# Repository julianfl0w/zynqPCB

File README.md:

# zynqPCB
An 8-layer board built upon Xilinx Zynq Chip. Includes sound output, HDMI, DDR3, USB Host, USB Device, a handful of sensors, and Arduino Uno style header for screen connection. See schematic in this repo "schematic.pdf"
  
## OPEN TO COLLABORATION!!

# Kicad Project
  
https://kicad.org/  

# 3D Render

# Layout

# Block Diagram 

# Manufactured PCB - Top

# Manufactured PCB - Bottom

# Introduction  
Hi friends! This is the current status of my 4-year project to make an FPGA-accelerated audio+video synthesizer. I am currently taking a hiatus from this project, and have decided to make the entire PCB design available on Github! Quite a bit of work has been put into this project. The difficult tasks of part selection and routing have been taken care of. I am still testing the functionality of the board. Only one PCB problem has been found: the SPI Flash for Zynq Boot was the wrong footprint! This problem has since been fixed.  

I believe that together we can make this a formidable tool in the open hardware community.  

The following software projects need to be undertaken before this project is usable by the general public:
1. Development of Boot firmware for the SPI flash which loads the linux kernel from the SD card
2. Development of a basic shell block diagram in Vivado  
  
If you embark on one of these projects, please share your code here so other engineers don't have to reproduce your work :)  

# IMPORTANT: Make sure to clone the following into the same directory:
https://github.com/julianfl0w/footprints.pretty  
https://github.com/julianfl0w/lib  
  
## I make no guarantees as to device funtionality. Please review the board carefully before production. 
Specific hardware (from BOM)  
xc7z020clg484 (Zynq Chip)  
VL53L1CXV0FY/1 (rangefinder)  

# Interfaces:  
1. JTAG interface : Functional!
2. SPI Flash : Untested
3. VL53L1CXV0FY Rangefinder : Untested  
4. APDS-9960 Rangefinder : Untested 
5. LIS2HH12 Accelerometer : Untested 
6. LSM6DSLTR IMU  : Untested 
7. HDMI Out : Untested
8. USB Host : Untested
9. USB Device : Untested
10. DDR3 PS Memory : Untested
11. TLV320 Audio Codec : Untested
12. MicroSD card : Untested

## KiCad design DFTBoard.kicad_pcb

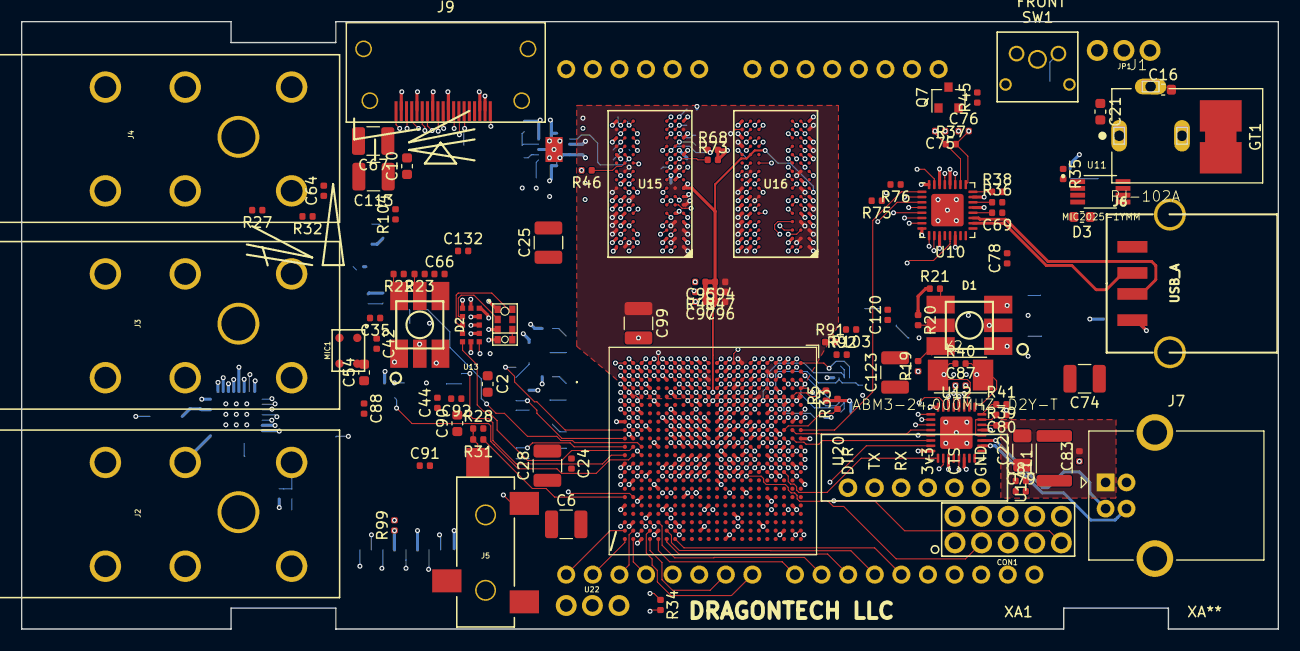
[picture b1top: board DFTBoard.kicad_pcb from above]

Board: 8 copper layers, 120.0 x 58.0 mm, 287 parts (0 on the bottom side), 295 nets.

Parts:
C1, C4, C8, C14, C15, C17, C18, C23, C29, C30, C31, C34, C46, C47, C50, C55, C65, C78, C87, C101, C102, C103, C104, C116, C117, C118, C119, C121: .47uF; C_0402_1005Metric
C2, C3, C10, C11, C13, C16, C21, C26, C33, C41, C51, C54, C58, C60, C90, C107, C125, C126, C128, C129, C130: 10uF; C_0603_1608Metric
C5, C9, C19, C20, C24, C27, C42, C57, C59, C66, C83, C89, C100, C114, C115, C122, C127: 4.7uF; C_0402_1005Metric
C6, C12, C25, C28, C67, C73, C74, C99, C123: 100uF; C_1210_3225Metric
C7, C32, C61, C109: 47uF; C_0805_2012Metric
C22: 330uF; C_1206_3216Metric
C35, C69, C80: 2.2uF; C_0402_1005Metric
C36, C39, C52, C53, C56, C62, C63, C64, C68, C70, C71, C72, C77, C79, C81, C82, C86, C88, C94, C95, C96, C97, C108, C131: .1uF; C_0402_1005Metric
C37, C38, C40, C43, C44, C45, C91, C92: 1uF; C_0402_1005Metric
C48, C49: 220uF Tant.; CP_EIA-3528-12_Kemet-T
C75, C76, C84, C85: 18pF; C_0402_1005Metric
C93, C98, C105, C106, C120, C132: .01uF; C_0402_1005Metric
C113: 47uF; C_1210_3225Metric
CON1: AVR-JTAG-10; XilinxJTAG
D1, D2: LED_RGB; PLCC6-SM-RGB-LED
D3, D4, D5, D6, D7: BLUE LED; C_0603_1608Metric
FB1: 120Ω @ 100 MHz, size 0603; C_0603_1608Metric
GT1: GNDTIE; gndtie
J1: PJ-102A; CUI_PJ-102A
J2, J3, J4: AUDIO JACK; RA49C14B
J5: JACK_TRS_4PINS; SJ-352X-SMT
J6: USB_A; USB-A-Receptacle-FCI_87583
J7: USB_B; USB_B_OST_USB-B1HSxx_Horizontal
J8: Micro_SD_Card_Det; AMPHENOL-114-00841-68
J9: HDMI_A; 10029449-111RLF
JP1: Jumper_3_Open; JUMPER_3PIN
L1, L2, L3, L4, L5: 2.2uH; C_1812_4532Metric
MIC1: MEMSMIC; WM7121PE
Q1, Q2, Q3, Q4, Q5, Q6, Q7, Q8, Q9, Q10: IRLML2502; SOT-23
R1, R2, R3, R4, R5, R17, R27, R28, R29, R101: 100k; R_0402_1005Metric
R6, R26, R33, R36, R39, R42, R43, R44: 10k; R_0402_1005Metric
R7, R46, R49: 240 1%; R_0402_1005Metric
R8, R9, R10, R74, R98, R103, R104: 4.7k; R_0402_1005Metric
R11, R12, R13, R14, R15, R16, R19, R20, R22, R23: 100; R_0402_1005Metric
R18, R30, R31, R32: 49.9k; R_0402_1005Metric
R21, R24, R35, R45, R78, R80, R86, R102: 150; R_0402_1005Metric
R25, R91, R92, R93, R94, R95, R96, R97: 20k; R_0402_1005Metric
R34: 47; R_0402_1005Metric
R37, R40: 1M; R_0402_1005Metric
R38, R41, R82: 8.06k 1%; R_0402_1005Metric
R47, R48: 10k 1%; R_0402_1005Metric
R50: 80.6 1%; R_0402_1005Metric
R51, R52, R53, R54, R55, R56, R57, R58, R59, R60, R61, R62, R63, R64, R65, R66, R67, R68, R69, R70, R71, R72, R73: 40.2 1%; R_0402_1005Metric
R75, R76: 80.6; R_0402_1005Metric
R77, R79, R85: 1k; R_0402_1005Metric
R81: 44.65k 1%; R_0402_1005Metric
R99: 47k; R_0402_1005Metric
R100: 24.9 1%; R_0402_1005Metric
SW1: TL6215RF200BDT; tl6215_right_angle
U1, U2: LM3880; SOT-23-6
U3: SC189 - 1.0V; SOT-23-5
U4: SC189 - 3.3V; SOT-23-5
U5: TLV62080DSGx; WSON-8-1EP_2x2mm_P0.5mm_EP0.9x1.6mm
U6: TPS562209DDCT
U7: SC189 - 1.8V; SOT-23-5
U8: TPS51200DRCR; VSON-10-1EP_3x3mm_P0.5mm_EP1.65x2.4mm_ThermalVias
U9: TLV320AIC3104; QFN-32-1EP_5x5mm_P0.5mm_EP3.65x3.65mm
U10, U12: USB3320; QFN-32-1EP_5x5mm_P0.5mm_EP3.1x3.1mm
U11: MIC2025-1YMM; SOP65P490X110-8N
U13: VL53L0X; Optical_LGA12
U14: APDS-9960; APDS_9960
U15, U16: MT41K256M16HA-125_E; FBGA-96-DDR3-SDRAM
U17: FTDITypeUART; FTDI_CONN
U18: ABRACON-ASDMB; XTAL_ASDMB-24.000MHZ-LC-T
U19: S25FL256SAGNFI001; WSON-8
U20: xc7z020clg484; BGA-484_19.0x19.0mm_Layout22x22_P0.80mm_dia0.40mm
U22: TSOP344; JUMPER_3PIN
XA1: Arduino_Uno_Shield_Simplified
Y1, Y2: ABM3-24.000MHZ-D2Y-T; XTAL500X320X130N

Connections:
1v0en: R1.2, U1.6, U3.3
1v8en: R2.2, U1.5, U7.3
1v35PG: U5.6, U20.D7
1v35en: R4.2, U2.5, U5.1
3v3en: R3.2, U2.6, U4.3
+1V0: C8.1, C9.1, C11.1, C12.1, C14.1, C15.1, C17.1, C18.1, C19.1, C20.1, C22.1, C27.1, C28.1, C29.1, C30.1, C31.1, L3.2, U3.4, U20.G8, U20.H9, U20.H11, U20.J8, U20.J10, U20.J12, U20.J14, U20.K13, U20.L8, U20.L14, U20.M13, U20.N8, U20.N14, U20.P13, U20.R8, U20.R14
+1V8: C4.1, C5.1, C6.1, C23.1, C24.1, C25.1, C26.1, C32.1, C51.1, C53.1, C78.1, C87.1, CON1.4, FB1.2, L4.2, R9.2, R10.2, R17.1, R27.2, R28.2, R29.2, R44.1, U7.4, U9.32, U10.28, U10.30, U12.28, U12.30, U20.K9, U20.K11, U20.L10, U20.M9, U20.N10, U20.P9, U20.P11, U20.R10, U20.R12, U20.T7, U20.T8, U20.T9, U20.T10
+1V35: C7.1, C94.1, C96.1, C99.1, C100.1, C101.1, C102.1, C103.1, C104.1, C125.1, C126.1, L1.2, R6.2, R47.1, R75.2, U5.5, U8.2, U15.A1, U15.A8, U15.B2, U15.C1, U15.C9, U15.D2, U15.D9, U15.E9, U15.F1, U15.G7, U15.H2, U15.H9, U15.K2, U15.K8, U15.N1, U15.N9, U15.R1, U15.R9, U16.A1, U16.A8, U16.B2, U16.C1, U16.C9, U16.D2, U16.D9, U16.E9, U16.F1, U16.G7, U16.H2, U16.H9, U16.K2, U16.K8, U16.N1, U16.N9, U16.R1, U16.R9, U20.E2, U20.F5, U20.H1, U20.J4, U20.K7, U20.M3, U20.N6, U20.R2, U20.V1
+3V3: C10.1, C39.2, C41.2, C46.1, C47.1, C50.1, C52.2, C54.2, C55.1, C56.2, C57.1, C58.2, C59.1, C60.1, C61.1, C62.1, C65.1, C66.1, C67.1, C68.1, C70.1, C71.1, C79.1, C81.1, C82.1, C88.1, C89.1, C90.2, C91.2, C92.2, C113.1, C114.1, C115.1, C116.1, C117.1, C118.1, C119.1, C120.1, C121.1, C122.1, C123.1, C127.2, C132.1, J8.4, L2.2, R5.1, R25.1, R33.2, R42.1, R43.1, R95.2, R98.2, R99.1, R101.1, R102.2, R103.1, R104.1, U4.4, U8.10, U9.7, U9.18, U9.24, U9.25, U10.8, U10.11, U10.14, U10.32, U12.8, U12.11, U12.14, U12.32, U13.1, U13.11, U14.5, U14.8, U17.3, U18.4, U19.8, U20.A10, U20.AA10, U20.AA20, U20.AB3, U20.AB13, U20.B3, U20.B13, U20.C6, U20.D9, U20.E12, U20.T5, U20.U8, U20.U18, U20.V11, U20.V21, U20.W4, U20.W14, U20.Y7, U20.Y17, U22.3, XA1.3V3, XA1.IORF
+5V: C2.1, C3.1, C13.1, C43.1, C44.1, C72.1, C77.1, C86.1, J9.18, JP1.2, R1.1, R2.1, R3.1, R4.1, R19.1, R20.1, R21.1, R22.1, R23.1, R24.1, R35.2, R45.1, R78.1, R80.2, R86.2, U1.1, U2.1, U3.1, U4.1, U5.8, U7.1, U10.21, U11.7, U12.21, XA1.5V1, XA1.VIN
/Audio/HPRCOM_MC: C49.2, J5.2
/Audio/HPRCOM_PC: C48.2, J5.3
/Audio/HPSWITCH: J5.4, R28.1, R31.2
/Audio/INSWITCH: J2.TB, R17.2, R18.2
/Audio/JACK_INC_N: C40.1, U9.11
/Audio/JACK_INC_P: C37.1, U9.10
/Audio/JACK_IN_N: C40.2, J2.R
/Audio/JACK_IN_P: C37.2, J2.T
/Audio/LED_1BA: D1.4, R21.2
/Audio/LED_1BC: D1.3, Q5.3
/Audio/LED_1GA: D1.5, R20.2
/Audio/LED_1GC: D1.2, Q3.3
/Audio/LED_1RA: D1.6, R19.2
/Audio/LED_1RC: D1.1, Q1.3
/Audio/LED_2BA: D2.4, R24.2
/Audio/LED_2BC: D2.3, Q6.3
/Audio/LED_2GA: D2.5, R23.2
/Audio/LED_2GC: D2.2, Q4.3
/Audio/LED_2RA: D2.6, R22.2
/Audio/LED_2RC: D2.1, Q2.3
/Audio/LSWITCH: J3.TB, R29.1, R30.2
/Audio/MICBIAS: C35.2, C42.1, MIC1.1, U9.15
/Audio/RSWITCH: J4.TB, R27.1, R32.2
/Audio/SIGC_F: C38.2, MIC1.4
/Audio/SIG_F: C38.1, U9.12
/DDR3/PGOOD_LED: D7.2, R102.1
/DDR3/VREF: C93.1, C94.2, C95.1, C96.2, C97.1, C98.1, C105.1, C106.1, R47.2, R48.1, U8.1, U15.H1, U15.M8, U16.H1, U16.M8, U20.H7, U20.P7
/DDR3/ZQH: R46.1, U15.L8
/DDR3/ZQL: R49.1, U16.L8
/LCD50/SLED0_D: D4.1, Q8.3
/LCD50/SLED0_G: Q8.1, R77.1
/LCD50/SLED0_R: D4.2, R78.2
/LCD50/SLED1_D: D5.1, Q9.3
/LCD50/SLED1_G: Q9.1, R79.1
/LCD50/SLED1_R: D5.2, R80.1
/LCD50/SLED2_D: D6.1, Q10.3
/LCD50/SLED2_G: Q10.1, R85.1
/LCD50/SLED2_R: D6.2, R86.1
/Power/1V0TOLX: L3.1, U3.5
/Power/1V8TOLX: L4.1, U7.5
/Power/3V3TOLX: L2.1, U4.5
/Sensors/TEMPO_LED_D: Q7.3, SW1.3
/Sensors/TEMPO_LED_R: R45.2, SW1.4
/USB/USBH_FLAG_LED: D3.2, R35.1
AX_TCLK: CON1.1, U20.G11
AX_TDI: CON1.9, U20.H13
AX_TDO: CON1.3, U20.G14
AX_TMS: CON1.5, U20.G12
BOOTSPI_CS: U19.1, U20.A1
BOOTSPI_DQ0_BMODE3: R92.1, U19.5, U20.A2
BOOTSPI_DQ1_BMODE1: R94.1, U19.2, U20.F6
BOOTSPI_DQ2_BMODE2: R93.1, U19.3, U20.E4
BOOTSPI_DQ3_BMODE0: R95.1, U19.7, U20.A3
BOOTSPI_SCK_BMODE4: R91.1, U19.6, U20.A4
CLK33.33: R100.2, U18.3
DDR3_A0: R51.1, U15.N3, U16.N3, U20.M4
DDR3_A1: R52.1, U15.P7, U16.P7, U20.M5
DDR3_A2: R53.1, U15.P3, U16.P3, U20.K4
DDR3_A3: R54.1, U15.N2, U16.N2, U20.L4
DDR3_A4: R55.1, U15.P8, U16.P8, U20.K6
DDR3_A5: R56.1, U15.P2, U16.P2, U20.K5
DDR3_A6: R57.1, U15.R8, U16.R8, U20.J7
DDR3_A7: R58.1, U15.R2, U16.R2, U20.J6
DDR3_A8: R59.1, U15.T8, U16.T8, U20.J5
DDR3_A9: R60.1, U15.R3, U16.R3, U20.H5
DDR3_A10: R61.1, U15.L7, U16.L7, U20.J3
DDR3_A11: R62.1, U15.R7, U16.R7, U20.G5
DDR3_A12: R63.1, U15.N7, U16.N7, U20.H4
DDR3_A13: R64.1, U15.T3, U16.T3, U20.F4
DDR3_A14: R65.1, U15.T7, U16.T7, U20.G4
DDR3_BA0: R66.1, U15.M2, U16.M2, U20.L7
DDR3_BA1: R67.1, U15.N8, U16.N8, U20.L6
DDR3_BA2: R68.1, U15.M3, U16.M3, U20.M6
DDR3_CAS#: R70.1, U15.K3, U16.K3, U20.P3
DDR3_CKE: U15.K9, U16.K9, U20.V3
DDR3_CK_N: R50.2, U15.K7, U16.K7, U20.N5
DDR3_CK_P: R50.1, U15.J7, U16.J7, U20.N4
DDR3_CS#: R73.1, U15.L2, U16.L2, U20.P6
DDR3_DM0: U16.E7, U20.B1
DDR3_DM1: U16.D3, U20.H3
DDR3_DM2: U15.E7, U20.P1
DDR3_DM3: U15.D3, U20.AA2
DDR3_DQ0: U16.H7, U20.D1
DDR3_DQ1: U16.E3, U20.C3
DDR3_DQ2: U16.F2, U20.B2
DDR3_DQ3: U16.G2, U20.D3
DDR3_DQ4: U16.H3, U20.E3
DDR3_DQ5: U16.H8, U20.E1
DDR3_DQ6: U16.F7, U20.F2
DDR3_DQ7: U16.F8, U20.F1
DDR3_DQ8: U16.A2, U20.G2
DDR3_DQ9: U16.A3, U20.G1
DDR3_DQ10: U16.C3, U20.L1
DDR3_DQ11: U16.C8, U20.L2
DDR3_DQ12: U16.D7, U20.L3
DDR3_DQ13: U16.A7, U20.K1
DDR3_DQ14: U16.C2, U20.J1
DDR3_DQ15: U16.B8, U20.K3
DDR3_DQ16: U15.F2, U20.M1
DDR3_DQ17: U15.E3, U20.T3
DDR3_DQ18: U15.G2, U20.N3
DDR3_DQ19: U15.F7, U20.T1
DDR3_DQ20: U15.H7, U20.R3
DDR3_DQ21: U15.F8, U20.T2
DDR3_DQ22: U15.H3, U20.M2
DDR3_DQ23: U15.H8, U20.R1
DDR3_DQ24: U15.D7, U20.AA3
DDR3_DQ25: U15.A2, U20.U1
DDR3_DQ26: U15.A7, U20.AA1
DDR3_DQ27: U15.A3, U20.U2
DDR3_DQ28: U15.C2, U20.W1
DDR3_DQ29: U15.C8, U20.Y3
DDR3_DQ30: U15.B8, U20.W3
DDR3_DQ31: U15.C3, U20.Y1
DDR3_DQS0_N: U16.G3, U20.D2
DDR3_DQS0_P: U16.F3, U20.C2
DDR3_DQS1_N: U16.B7, U20.J2
DDR3_DQS1_P: U16.C7, U20.H2
DDR3_DQS2_N: U15.G3, U20.P2
DDR3_DQS2_P: U15.F3, U20.N2
DDR3_DQS3_N: U15.B7, U20.W2
DDR3_DQS3_P: U15.C7, U20.V2
DDR3_DRST#: R74.1, U15.T2, U16.T2, U20.F3
DDR3_ODT: R72.1, U15.K1, U16.K1, U20.P5
DDR3_RAS#: R69.1, U15.J3, U16.J3, U20.R5
DDR3_VTT: C128.1, C129.1, C130.1, R51.2, R52.2, R53.2, R54.2, R55.2, R56.2, R57.2, R58.2, R59.2, R60.2, R61.2, R62.2, R63.2, R64.2, R65.2, R66.2, R67.2, R68.2, R69.2, R70.2, R71.2, R72.2, R73.2, U8.3, U8.5
DDR3_VTT_EN: R25.2, U8.7, U20.B6
DDR3_WE#: R71.1, U15.L3, U16.L3, U20.R4
GND: C1.2, C2.2, C3.2, C4.2, C5.2, C6.2, C7.2, C8.2, C9.2, C10.2, C11.2, C12.2, C13.2, C14.2, C15.2, C16.2, C17.2, C18.2, C19.2, C20.2, C21.2, C22.2, C23.2, C24.2, C25.2, C26.2, C27.2, C28.2, C29.2, C30.2, C31.2, C32.2, C33.2, C34.2, C39.1, C41.1, C43.2, C44.2, C46.2, C47.2, C50.2, C51.2, C53.2, C55.2, C57.2, C59.2, C61.2, C63.2, C64.2, C65.2, C66.2, C67.2, C68.2, C69.1, C70.2, C71.2, C72.2, C73.1, C74.1, C75.1, C76.1, C77.2, C78.2, C79.2, C80.1, C81.2, C82.2, C83.1, C84.1, C85.1, C86.2, C87.2, C88.2, C89.2, C90.1, C91.1, C92.1, C93.2, C95.2, C97.2, C98.2, C99.2, C100.2, C101.2, C102.2, C103.2, C104.2, C105.2, C106.2, C107.2, C109.2, C113.2, C114.2, C115.2, C116.2, C117.2, C118.2, C119.2, C120.2, C121.2, C122.2, C123.2, C125.2, C126.2, C127.1, C128.2, C129.2, C130.2, C131.2, C132.2, CON1.2, CON1.10, GT1.1, J1.2, J6.4, J6.5, J7.4, J7.5, J8.6, J8.10, J8.11, J9.2, J9.5, J9.8, J9.11, J9.17, J9.SH, Q1.2, Q2.2, Q3.2, Q4.2, Q5.2, Q6.2, Q7.2, Q8.2, Q9.2, Q10.2, R8.2, R38.2, R41.2, R46.2, R48.2, R49.2, R74.2, R76.2, R82.2, R91.2, R92.2, R93.2, R94.2, R96.2, R97.2, SW1.1, U1.2, U2.2, U3.2, U4.2, U5.2, U5.3, U5.9, U6.1, U7.2, U8.4, U8.8, U8.11, U9.6, U9.33, U10.23, U10.33, U11.3, U12.33, U13.2, U13.3, U13.4, U13.6, U13.12, U14.6, U15.A9, U15.B1, U15.B3, U15.B9, U15.D1, U15.D8, U15.E1, U15.E2, U15.E8, U15.F9, U15.G1, U15.G8, U15.G9, U15.J2, U15.J8, U15.M1, U15.M9, U15.P1, U15.P9, U15.T1, U15.T9, U16.A9, U16.B1, U16.B3, U16.B9, U16.D1, U16.D8, U16.E1, U16.E2, U16.E8, U16.F9, U16.G1, U16.G8, U16.G9, U16.J2, U16.J8, U16.M1, U16.M9, U16.P1, U16.P9, U16.T1, U16.T9, U17.1, U18.2, U19.4, U20.A5, U20.A15, U20.AA5, U20.AA15, U20.AB8, U20.AB18, U20.B8, U20.B18, U20.C1, U20.C11, U20.C21, U20.D4, U20.D14, U20.E7, U20.E17, U20.F10, U20.F20, U20.G3, U20.G9, U20.G10, U20.H6, U20.H8, U20.H12, U20.H14, U20.H16, U20.J9, U20.J11, U20.J13, U20.J19, U20.K2, U20.K8, U20.K10, U20.K12, U20.K14, U20.K22, U20.L5, U20.L9, U20.L11, U20.L12, U20.L13, U20.L15, U20.M8, U20.M10, U20.M11, U20.M12, U20.M14, U20.M18, U20.N1, U20.N9, U20.N11, U20.N12, U20.N13, U20.N21, U20.P4, U20.P8, U20.P10, U20.P12, U20.P14, U20.R9, U20.R11, U20.R13, U20.R17, U20.T13, U20.T20, U20.U3, U20.U13, U20.V6, U20.V16, U20.W9, U20.W19, U20.Y2, U20.Y12, U20.Y22, U22.2, XA1.GND1, XA1.GND2, XA1.GND3
GNDA: C35.1, C36.1, C42.2, C45.1, C52.1, C54.1, C56.1, C58.1, C60.2, C62.2, GT1.2, J2.RB, J2.S, J3.RB, J3.S, J4.RB, J4.S, J5.1, MIC1.2, MIC1.3, U9.17, U9.21, U9.26
HDMI_B_N: J9.3, U20.AA8
HDMI_B_P: J9.1, U20.AA9
HDMI_CEC: J9.13, U20.W5
HDMI_CLK_N: J9.12, U20.Y8
HDMI_CLK_P: J9.10, U20.Y9
HDMI_G_N: J9.6, U20.AA6
HDMI_G_P: J9.4, U20.AA7
HDMI_HEAC_N: J9.19, U20.AB6
HDMI_HEAC_P: J9.14, U20.AB7
HDMI_R_N: J9.9, U20.Y5
HDMI_R_P: J9.7, U20.Y6
HPCOM_N: C48.1, U9.20
HPCOM_P: C49.1, U9.22
I2C33_SCLK: J9.15, R103.2, U9.8, U13.10, U14.7, U20.C5
I2C33_SDA: J9.16, U13.9, U14.1, U20.A6
I2C33_SDIN: R104.2, U9.9
I2S_ADCSD: U9.5, U20.AB15
I2S_BCLK: U9.2, U20.AA13
I2S_DACSD: U9.4, U20.Y14
I2S_LRCLK: U9.3, U20.AB14
I2S_MCLK: U9.1, U20.Y13
INIT_B: R10.1, U20.T14
IR_RX: U20.AB20, U22.1
JD_HOUT: R31.1, U20.AB17
JD_IN: C36.2, R18.1, U20.U17
JD_LOUT: C63.1, R30.1, U20.W16
JD_ROUT: C64.1, R32.1, U20.V17
LCD_D0: U20.AB21, XA1.D0
LCD_D1: U20.AB22, XA1.D1
LCD_D2: U20.U19, XA1.SCL
LCD_D3: U20.W20, XA1.SDA
LCD_D4: U20.V5, XA1.A5
LCD_D5: U20.AB5, XA1.A4
LCD_D6: U20.AB4, XA1.A3
LCD_D7: U20.AA4, XA1.A2
LCD_D8: U20.Y4, XA1.A1
LCD_D9: U20.AB2, XA1.A0
LCD_D10: U20.U20, XA1.AREF
LCD_D11: U20.AA21, XA1.D2
LCD_D12: U20.AA22, XA1.D3
LCD_D13: U20.Y21, XA1.D4
LCD_D14: U20.Y20, XA1.D5
LCD_D15: U20.W22, XA1.D6
LCD_D16: U20.W21, XA1.D7
LCD_D17: U20.V22, XA1.D8
LCD_D18: U20.V20, XA1.D9
LCD_D19: U20.U22, XA1.D10
LCD_D20: U20.U21, XA1.D11
LCD_D21: U20.T22, XA1.D12
LCD_D22: U20.T21, XA1.D13
LCD_D23: U20.AB1, XA1.RST1
LED_1B_CTRL: R15.2, U20.W13
LED_1G_CTRL: R13.2, U20.V14
LED_1R_CTRL: R11.2, U20.V13
LED_2B_CTRL: R16.2, U20.AB12
LED_2G_CTRL: R14.2, U20.Y11
LED_2R_CTRL: R12.2, U20.AA12
LOUT_N: J3.R, U9.28
LOUT_P: J3.T, U9.27
unnamed: C1.1, U1.3
unnamed: C33.1, C34.1, FB1.1, U20.H10
unnamed: C45.2, U9.13
unnamed: C69.2, U10.20
unnamed: C75.2, R37.1, U10.26, Y1.1
unnamed: C76.2, R37.2, U10.25, Y1.2
unnamed: C80.2, U12.20, U12.23
unnamed: C84.2, R40.1, U12.26, Y2.1
unnamed: C85.2, R40.2, U12.25, Y2.2
unnamed: C16.1, C107.1, J1.1, R26.1, U6.3
unnamed: C108.1, L5.1, U6.2
unnamed: C108.2, U6.6
unnamed: C21.1, C109.1, JP1.1, L5.2, R81.1
unnamed: C131.1, U8.6
unnamed: D3.1, U11.2
unnamed: D7.1, R101.2, U8.9
unnamed: L1.1, U5.7
unnamed: Q1.1, R11.1
unnamed: Q2.1, R12.1
unnamed: Q3.1, R13.1
unnamed: Q4.1, R14.1
unnamed: Q5.1, R15.1
unnamed: Q6.1, R16.1
unnamed: R6.1, R7.1, U5.4
unnamed: R7.2, R8.1
unnamed: R26.2, U6.5
unnamed: R33.1, U20.C9
unnamed: R34.1, U20.D6
unnamed: R36.1, U10.22
unnamed: R38.1, U10.24
unnamed: R39.1, U12.22
unnamed: R41.1, U12.24
unnamed: R42.2, U13.5
unnamed: R75.1, U20.M7
unnamed: R76.1, U20.N7
unnamed: R81.2, R82.1, U6.4
unnamed: R98.1, U18.1
unnamed: R100.1, U20.F7
unnamed: U1.4, U2.3
unnamed: U14.3, U14.4
PROGRAM_B: R9.1, U20.T11
RF2_IRQ: U14.2, U20.E6
RF_IRQ: R43.2, U13.7, U20.AA11
ROUT_N: J4.R, U9.30
ROUT_P: J4.T, U9.29
SD_CD: J8.9, R99.2, U20.A13
SD_CLK: J8.5, R34.2
SD_CMD: J8.3, U20.E9
SD_D0: J8.7, U20.A7
SD_D1: J8.8, U20.E10
SD_D2: J8.1, U20.A8
SD_D3: J8.2, U20.F11
STATLED_0: R77.2, U20.AB11
STATLED_1: R79.2, U20.AB10
STATLED_2: R85.2, U20.AB9
TEMPO_LED: Q7.1, U20.V9
TEMPO_SW: R44.2, SW1.2, U20.V15
TLV_RST#: U9.31, U20.AA17
UART33_RX: U17.4, U20.G7
UART33_TX: U17.5, U20.B4
USB0_CLK: U10.1, U20.A9
USB0_D0: U10.3, U20.C7
USB0_D1: U10.4, U20.G13
USB0_D2: U10.5, U20.B12
USB0_D3: U10.6, U20.F14
USB0_D4: U10.7, U20.A12
USB0_D5: U10.9, U20.B14
USB0_D6: U10.10, U20.F13
USB0_D7: U10.13, U20.C13
USB0_RST: U10.27, U20.D10
USB0_dir: U10.31, U20.E8
USB0_nxt: U10.2, U20.F9
USB0_stp: U10.29, U20.A11
USB1_CLK: U12.1, U20.D11
USB1_D0: U12.3, U20.E13
USB1_D1: U12.4, U20.B9
USB1_D2: U12.5, U20.D12
USB1_D3: U12.6, U20.B10
USB1_D4: U12.7, U20.E14
USB1_D5: U12.9, U20.C14
USB1_D6: U12.10, U20.D13
USB1_D7: U12.13, U20.C10
USB1_RST: U12.27, U20.C12
USB1_dir: U12.31, U20.C8
USB1_nxt: U12.2, U20.B11
USB1_stp: U12.29, U20.D8
USBD_D_N: J7.2, U12.19
USBD_D_P: J7.3, U12.18
USBD_VBUS: C83.2, J7.1, JP1.3, R39.2
USBH_CPEN: U10.17, U11.1
USBH_D_N: J6.2, U10.19
USBH_D_P: J6.3, U10.18
USBH_VBUS: C73.2, C74.2, J6.1, R36.2, U11.6, U11.8
VMODE0: R96.1, U20.D5
VMODE1: R97.1, U20.E5
ZYNQ_POR: R5.2, U2.4, U20.B5

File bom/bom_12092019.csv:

Refs,Value,Footprint,Quantity,MFR,MPN,SPR,SPN
Y1;Y2,24.000MHZ,ABM3-12.000MHZ-B2-T:XTAL500X320X130N,2,Abracon LLC,ABM3-24.000MHZ-D2Y-T,DigiKey,535-10643-2-ND
C106;C105;C98;C93;C109;C110;C120;C111,.01uF,Capacitor_SMD:C_0402_1005Metric,8,Murata,GRM155R71H103KA88J,Digikey,490-6351-1-ND
C68;C70;C71;C77;C72;C79;C81;C82;C86;C131;C97;C96;C95;C94;C88;C16;C107;C36;C64;C63;C52;C56;C53;C62;C39,.1uF,Capacitor_SMD:C_0402_1005Metric,25,Murata,GRM188R71C104KA01D,Digikey,490-1532-1-ND
C65;C78;C87;C34;C18;C17;C15;C14;C29;C30;C31;C23;C8;C4;C1;C108;C116;C117;C118;C119;C104;C103;C102;C101;C121;C55;C50;C47;C46,.47uF,Capacitor_SMD:C_0402_1005Metric,29,Murata,GRM188R71C474KA88D,Digikey,490-3295-1-ND
C76;C75;C85;C84,18pF,Capacitor_SMD:C_0402_1005Metric,4,Murata,GCM1555C1H180JA16D,Digikey,490-12650-1-ND
C91;C92;C37;C40;C38;C45;C43;C44,1uF,Capacitor_SMD:C_0402_1005Metric,8,Murata,GRM188R71C105KE15D,Digikey,490-10734-1-ND
C69;C80;C35,2.2uF,Capacitor_SMD:C_0402_1005Metric,3,Murata,GRM155R61A225KE95D,Digikey,490-10451-1-ND
C66;C83;C20;C19;C24;C27;C9;C5;C114;C115;C100;C127;C122;C89;C21;C42;C59;C57,4.7uF,Capacitor_SMD:C_0402_1005Metric,18,Murata,GRM21BR61A475KA73L,Digikey,490-9750-1-ND
C3;C13;C2;C10;C11;C26;C33;C126;C125;C130;C129;C128;C90;C54;C58;C51;C41;C60,10uF,Capacitor_SMD:C_0603_1608Metric,18,Murata,GRM21BR61A106KE19L,Digikey,490-1709-1-ND
FB1,"120R, 100 MHz, size 0603",Capacitor_SMD:C_0603_1608Metric,1,Murata Electronics,BLM18AG121SN1D,Digikey,490-1011-1-ND
D3;D5;D4;D6;D7,BLUE LED,Capacitor_SMD:C_0603_1608Metric,5,Vishay Semiconductors,VLMB1300-GS08,Digikey,VLMB1300-GS08CT-ND
C32;C7;C61,47uF,Capacitor_SMD:C_0805_2012Metric,3,Murata Manufacturing Co Ltd,GRM32ER70J476ME20L,Digikey,490-6542-1-ND
C22,330uF,Capacitor_SMD:C_1206_3216Metric,1,AVX Corporation,F950G337MAAAQ2,Digikey,478-8378-1-ND
C67;C73;C74;C28;C25;C12;C6;C99;C123,100uF,Capacitor_SMD:C_1210_3225Metric,9,TAIYO YUDEN,JMK325ABJ107MM-P,Digikey,587-4313-1-ND
C113,47uF,Capacitor_SMD:C_1210_3225Metric,1,Murata Manufacturing Co Ltd,GRM32ER70J476ME20L,Digikey,490-6542-1-ND
L2;L3;L4;L1,2.2uH,Capacitor_SMD:C_1812_4532Metric,4,Murata,LQH43PN2R2M26L,Digikey,490-12049-1-ND
C49;C48,220uF Tant.,Capacitor_Tantalum_SMD:CP_EIA-3528-12_Kemet-T,2,AVX Corporation,F930G227KBA,Digikey,478-8139-1-ND
J7,USB_B,Connector_USB:USB_B_OST_USB-B1HSxx_Horizontal,1,On Shore Technology,USB-B1HSW6,Digikey,ED2982-ND
J9,HDMI_A,DFTcustom:10029449-111RLF,1,Amphenol ICC,10029449-111RLF,Digikey,609-4614-1-ND
J8,Micro_SD_Card_Det,DFTcustom:AMPHENOL-114-00841-68,1,Amphenol ICC,114-00841-68,Digikey,114-00841-68-1-ND
U14,APDS-9960,DFTcustom:APDS_9960,1,Broadcom Limited,APDS-9960,Digikey,516-3480-1-ND
XA1,Arduino_Uno_Shield_Simplified,DFTcustom:Arduino_Uno_Shield_Simplified,1,DNS,-,-,-
U20,xc7z020clg484,DFTcustom:BGA-484_19.0x19.0mm_Layout22x22_P0.80mm_dia0.40mm,1,Xilinx,XC7Z020-1CLG484C,Digikey,122-1850-ND
U15;U16,MT41K256M16HA-125_E,DFTcustom:FBGA-96-DDR3-SDRAM,2,Micron,MT41K256M16TW-107,Digikey,557-2006-6-ND
U17,FTDITypeUART,DFTcustom:FTDI_CONN,1,DNS,-,-,-
U22,TSOP344,DFTcustom:JUMPER_3PIN,1,Vishay Semiconductor,TSOP34438,Digikey,TSOP34438-ND
U13,VL53L1CXV0FY/1,DFTcustom:Optical_LGA12,1,STMicroelectronics,VL53L1CXV0FY/1,Digikey,497-17764-2-ND
D1;D2,LED_RGB,DFTcustom:PLCC6-SM-RGB-LED,2,"Cree, Inc.",CLP6C-FKB-CM1Q1H1BB7R3R3,Digikey,CLP6C-FKB-CM1Q1H1BB7R3R3CT-ND
J4;J3;J2,AUDIO JACK,DFTcustom:RA49C14B,3,Switchcraft Conxall,RA49C12B,Digikey,SC2083-ND
J5,JACK_TRS_4PINS,DFTcustom:SJ-352X-SMT,1,CUI Inc.,SJ-3524-SMT-TR,Digikey,CP-3524SJCT-ND
J6,USB_A,DFTcustom:USB-A-Receptacle-FCI_87583,1,Amphenol ICC,87583-2010RLF,Digikey,609-5390-1-ND
MIC1,MEMSMIC,DFTcustom:WM7121PE,1,Cirrus Logic,WM7121PIMSE/RV,Digikey,WM7121PIMSE/RVCT-ND
U19,S25FL256SAGNFI001,DFTcustom:WSON-8,1,Cypress,S25FL256SAGNFI001,Digikey,1274-1005-ND
CON1,AVR-JTAG-10,DFTcustom:XilinxJTAG,1,DNS,,,
GT1,GNDTIE,DFTcustom:gndtie,1,DNS,-,-,-
SW1,TL6215RF200BDT,DFTcustom:tl6215_right_angle,1,E-Switch Inc,TL6215RF200BDT,Digikey,EG5162-ND 
U10;U12,USB3320,Package_DFN_QFN:QFN-32-1EP_5x5mm_P0.5mm_EP3.1x3.1mm,2,Microchip Technology,USB3320C-EZK-TR,Digikey,USB3320C-EZK-CT-NDs
U9,TLV320AIC3104,Package_DFN_QFN:QFN-32-1EP_5x5mm_P0.5mm_EP3.65x3.65mm,1,Texas Instruments,TLV320AIC3104IRHBR,Digikey,296-26818-1-ND
U6,LIS2HH12,Package_LGA:LGA-12_2x2mm_P0.5mm,1,STMicroelectronics,LIS2HH12TR,Digikey,497-15069-1-ND
U23,LSM6DS3,Package_LGA:LGA-14_3x2.5mm_P0.5mm_LayoutBorder3x4y,1,STMicroelectronics,LSM6DS3TR,Digikey,497-15383-1-ND
U21,PCA9306,Package_SO:SSOP-8_2.95x2.8mm_P0.65mm,1,Texas Instruments,PCA9306DCTR,Digikey,296-18509-2-ND
U8,TPS51200DRCR,Package_SON:VSON-10-1EP_3x3mm_P0.5mm_EP1.65x2.4mm_ThermalVias,1,Texas Instruments,TPS51200DRCR,Digikey,296-26978-1-ND
U5,TLV62080DSGx,Package_SON:WSON-8-1EP_2x2mm_P0.5mm_EP0.9x1.6mm,1,Texas Instruments,TLV62080DSGR,Digikey,296-39270-6-ND
Q9;Q8;Q10;Q7;Q5;Q3;Q1;Q6;Q4;Q2,IRLML2502,Package_TO_SOT_SMD:SOT-23,10,Infineon Technologies AG,IRLML2502TRPBF,Digikey,IRLML2502PBFCT-ND
U3,SC189 - 1.0V,Package_TO_SOT_SMD:SOT-23-5,1,Semtech Corporation,SC189ASKTRT,Digikey,SC189ASKCT-ND
U7,SC189 - 1.8V,Package_TO_SOT_SMD:SOT-23-5,1,Semtech Corporation,SC189LSKTRT,Digikey,SC189LSKCT-ND
U4,SC189 - 3.3V,Package_TO_SOT_SMD:SOT-23-5,1,Semtech Corporation,SC189ZSKTRT,Digikey,SC189ZSKCT-ND
U1;U2,LM3880,Package_TO_SOT_SMD:SOT-23-6,2,Texas Instruments,LM3880MF-1AE/NOPB,Digikey,LM3880MF-1AE/NOPBDKR-ND
R19;R20;R15;R13;R11;R22;R23;R16;R14;R12,100,Resistor_SMD:R_0402_1005Metric,10,Yageo,RC0402FR-07100RL,Digikey,311-100LRCT-ND
R1;R2;R3;R4;R5;R34;R81;R101;R27;R29;R17;R28,100k,Resistor_SMD:R_0402_1005Metric,12,Yageo,RC0402FR-07100KL,Digikey,311-100KLRTR-ND
R36;R39;R33;R6;R42;R43;R44,10k,Resistor_SMD:R_0402_1005Metric,7,Yageo,RC0402FR-0710KL,Digikey,311-10.0KLRTR-ND
R48;R47,10k 1%,Resistor_SMD:R_0402_1005Metric,2,Yageo,RC0402FR-0710KL,Digikey,311-10.0KLRCT-ND
R35;R80;R78;R86;R102;R45;R21;R24,150,Resistor_SMD:R_0402_1005Metric,8,Yageo,RC0402FR-07150RL,Digikey,311-150LRTR-ND
R37;R40,1M,Resistor_SMD:R_0402_1005Metric,2,Yageo,RC0402FR-071ML,Digikey,311-1.00MLRCT-ND
R79;R77;R85;R105,1k,Resistor_SMD:R_0402_1005Metric,4,Yageo,RC0402FR-071KL,Digikey,311-1.00KLRCT-ND
R25;R96;R97;R95;R91;R92;R93;R94;R106,20k,Resistor_SMD:R_0402_1005Metric,9,Yageo,RT0402BRD0720KL,Digikey,YAG1388CT-ND
R100,24.9 1%,Resistor_SMD:R_0402_1005Metric,1,Yageo,RC0402FR-0724K9L,Digikey,311-24.9KLRTR-ND
R7;R49;R46,240 1%,Resistor_SMD:R_0402_1005Metric,3,Yageo,RC0402FR-07240RL,Digikey,311-240LRTR-ND
R9;R10;R8;R82;R83;R74;R98;R103;R104,4.7k,Resistor_SMD:R_0402_1005Metric,9,Yageo,RC0402JR-074K7L,Digikey,311-4.7KJRCT-ND
R52;R51;R54;R53;R56;R55;R58;R57;R60;R59;R62;R61;R64;R63;R66;R65;R67;R68;R69;R70;R71;R72;R73,40.2 1%,Resistor_SMD:R_0402_1005Metric,23,Yageo,RC0402FR-0740R2L,Digikey,311-40.2LRTR-ND
R26;R84;R87,47,Resistor_SMD:R_0402_1005Metric,3,Yageo,RC0402JR-0747RL,Digikey,311-47JRTR-ND
R99,47k,Resistor_SMD:R_0402_1005Metric,1,Yageo,RC0402FR-0747KL,Digikey,311-47.0KLRTR-ND
R32;R30;R18;R31,49.9k,Resistor_SMD:R_0402_1005Metric,4,Yageo,RC0402FR-0749K9L,Digikey,311-49.9KLRCT-ND
R38;R41,8.06k 1%,Resistor_SMD:R_0402_1005Metric,2,Yageo,RC0402FR-078K06L,Digikey,311-8.06KLRTR-ND
R50;R75;R76,80.6 1%,Resistor_SMD:R_0402_1005Metric,3,Yageo,RC0402FR-0780R6L,Digikey,311-80.6LRTR-ND
R90;R88;R89,.05,Resistor_SMD:R_2512_6332Metric,3,Bourns Inc,CRA2512-FZ-R050ELF,Digikey,CRA2512-FZ-R050ELFCT-ND
U11,MIC2025-1YMM,SOP65P490X110-8N:SOP65P490X110-8N,1,Microchip,MIC2025-1YMM-TR,Digikey,MIC2025-1YMM-CT-ND
U18,ABRACON-ASDMB,XTAL_ASDMB-24.000MHZ-LC-T:XTAL_ASDMB-24.000MHZ-LC-T,1,Abracon LLC,ASDMB-24.000MHZ-LC-T,Digikey,535-11728-1-ND

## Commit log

2016-12-13 add xilinx7.lib
2016-12-13 add led driver library
2016-12-13 finished LED driver lib, added to LED page
2016-12-13 boutta merge yo
2016-12-15 addded audio codec library
2016-12-15 added spi flash library
2016-12-15 added i2c flash and voltage regs
2016-12-15 components are ro longer overlapping
2016-12-15 added cypress fx3 schematic symbol
2016-12-15 added rangefinder
2016-12-19 about to merge
2016-12-20 added some connections and passives
2016-12-22 basic FPGA and CyUSB connections
2016-12-22 finished configuration page of the FPGA
2016-12-22 near completion of GPIF II interface. placement of all FPGA components
2016-12-27 moved libraries into lib folder
2016-12-27 dereferenced some unused external libs
2016-12-27 added jack symbols and jack detection circuits
2016-12-27 added SPI/USB bridge
2016-12-28 updated gpios
2016-12-29 added HDMI, moved rotary encoders to USBSPI gpio
2016-12-29 added LED connections for LCD, created new SPI symbol
2016-12-29 misc
2016-12-29 made attachments for new spimem
2016-12-29 moved cypress power section
2016-12-31 a few changes persuant to FX3 PCB design recommendations
2017-01-02 added FX3 power caps
2017-01-02 added back HDMI
2017-01-02 connected all audio pins
2017-01-02 more power caps
2017-01-03 small changes
2017-01-03 renamed HDMI.sch reference to hdmi.sch
2017-01-03 connected jack detection signals to cypress
2017-01-03 changed jack detection pull up voltage to 3.3v
2017-01-03 connected out3 from audio chip to audio in of led chip
2017-01-03 added encoder page
2017-01-03 added I2S FPGA interface, finished most GPIO connections
2017-01-03 added back jack detection signals
2017-01-03 annotated
2017-01-03 fixed annotations
2017-01-03 changed i2c to i2s :)
2017-01-03 fixing some ERC errors
2017-01-03 edited components on HDMI and USB pages
2017-01-03 fixed encoder annotations
2017-01-03 reannotate
2017-01-03 any changes?
2017-01-09 resolved ERC errors, and began assigning footprints
2017-01-09 finished assigning cap footprints
2017-01-10 a few more footprints
2017-01-10 edited init_b and done LED circuits for FPGA config section
2017-01-10 forgot to save sch
2017-01-10 restored new LED circuits in FPGA config section
2017-01-10 new annotation
2017-01-10 edited LED resistor values
2017-01-10 added resistor footprints (1206)
2017-01-10 changed TS jacks to TRS
2017-01-10 annotated new audio connectors
2017-01-10 Made a few footprints
2017-01-10 started creating footprint for micro hdmi connector
2017-01-10 audio
2017-01-11 added back footprints
2017-01-12 finished hdmi port footprint
2017-01-12 fixed a few diagram/footprint pin mismatches, getting ready to pull gene's microhdmi footprint
2017-01-12 a bit of restructuring
2017-01-12 a few small changes
2017-01-12 merge
2017-01-12 fixing errors between footprints and schematics
2017-01-12 made some modifications to analog audio line
2017-01-12 moved gnd/vcc for hdmi chips
2017-01-12 fixed all schematic/footprint errors
2017-01-17 started PCBnew trivial connections and BGA interface, shuffled some net connections, etc.
2017-01-17 jan17 review
2017-01-17 jan17review
2017-01-17 annotate from scratch
2017-01-19 ran all FX3 BGA traces
2017-01-19 started adding jack
2017-01-19 added power jack detection and logic
2017-01-19 created footprint for power switch ic
2017-01-19 annotate?
2017-01-19 added pull down resistor to jack 5v, reannotated
2017-01-19 fixed diode polarity
2017-01-19 reannotated, created some footprints
2017-01-19 connected mic to MICBIAS
2017-01-19 fixed merge errors
2017-01-19 finished marking pin 1 on custom footprints
2017-01-23 more moving around components and connecting. all cypress and FPGA bypass caps placed
2017-01-25 finished wiring GPIF with exception of PCLK
2017-01-26 changed USB downstream ports to a single stacked receptacle
2017-01-26 finished a quarter to a third of non-priority connections
2017-01-26 more trivial connections and placements. swapped micro-hdmi for standard hdmi recepticle
2017-01-30 finished most non-priority connections and placed power/gnd planes
2017-01-30 all non-power wires connected and satisfactory. all that remains is a rework of power distribution
2017-01-30 everything tolerable except some questionable filled areas on bottom layer. still need to revise ground tie
2017-01-31 donegit add -Agit add -Agit add -A?
2017-01-31 added some edge divets to support mounting
2017-01-31 created output directory and outputs
2017-01-31 small changes, if any
2017-02-02 changed led driver footprint, added the appropriate amount of clearence for audio jacks, redid all those connections, etc, etc
2017-02-02 completed BOM, changed footprints and values of identical components (ex. 100nf -> .1uF), have yet to update PCBNEW to reflect footprint changes
2017-02-02 fixed PCB to reflect footprint changes
2017-02-02 fixed potentially debilitating pin mismatch on FX3 crystal, changed SSRX lines to be on SIG1
2017-02-03 straightened some traces
2017-02-03 fixed edge.cuts and mounting holes
2017-02-03 added configuration data line, other small changes
2017-02-08 rotated codec such that fewer digital/analog crossings occur
2017-02-08 updated gerbers
2017-02-10 thickened USB sig traces, centered footprints, and other small changes
2017-02-14 added accessable jumper for FX3 UART tx for potential debugging
2017-02-14 moved USB traces further from recept. pins, completed BOM with Bitelle Free Passives
2017-02-16 updated crystals to higher drive level and moved audio codec to right
2017-02-17 swapped 0201s for 0402 packages, currently reworking PDS so that 3.3V and 1.8V layers can be eliminated
2017-02-17 3.3V and 1.8V layers can now be deleted. Just need to figure out how... have a wonderful weekend all
2017-02-20 successfully switched to 8 layers, pushed out connectors to hang over the board more, filled signal layers with copper
2017-02-20 some small fixes
2017-02-21 changed via and trace widths to make this a 4mil/4mil board. moved more caps onto back of FPGA. added hardware for doubling line input as pedal input
2017-02-24 untented the vias
2017-03-06 some very minor fixes
2017-03-13 forced insert on J7, HDMI connector
2017-03-28 fixed tps22 land pattern issue. perhaps some other small fixes
2017-03-28 reduced CODEC voltage from 3v3 to 1.8v
2017-03-28 swapped pins 3 and 4 of crystal
2017-05-03 relocation of components for second prototype run, replacement of LCD with 50-pin ZIF connector for ILI9341
2017-05-04 boutta merge and accept theirs
2017-05-05 now featuring USB debugger in Python
2017-05-08 boutta merge
2017-08-10 encoders and headphone jack have been modified. many unconnections
2017-08-11 screen attached!
2017-08-11 same as before but without unconnected or DRC errors
2017-08-11 just need to do the BOM before sending HW2 to PCBWAY
2017-08-11 ancient linux commit
2017-08-11 using BOMs AWAY to create BOM
2017-08-12 just added NOTE field to BOMS AWAY
2017-08-12 Complete BOM. all resistors now 0402
2017-08-14 added caps to audio
2017-08-30 about to revert this commit
2017-08-30 Revert "about to revert this commit"
    This reverts commit fbbdb85fc73c11d2768e9943d86ff1ed088b3123.
2017-08-30 attached RAM_ODT signal
2017-12-14 about to sed replace all grounds with GND
2017-12-18 about to resize all silkscreen text to 0.5
2017-12-20 about to reduce text size again
2018-01-05 about to remove 2.4ghz radio, which complicates compliance and is redundant to MIDI over BLE over USB
2018-01-20 about to muntz out a) IR receiver b) 2.4Ghz receiver c) USB hub
2018-01-29 about to a) add back SDRAM b) reorganize parts/ reroute all traces
2018-02-08 added and length-matched DDR2 ram, compliant to Xilinx MIG
2018-02-13 all high speed busses added
2018-03-05 SD interface is verified and length-matched. about to increase annular ring size
2018-03-16 as submitted
2018-03-20 first revision with PCBWAY
2018-03-27 changes from fla
2019-03-03 removed artix7 and fx3 shizz, inserted Zynq7020
2019-03-04 added Zynq7020 and listed all tasks outstanding
2019-04-03 passes ERC, about to update footprints to v5 references
2019-04-05 replacing rescue components foreal
2019-04-05 still works, miraculously
2019-05-10 random updates
2019-05-12 everything placed, about to shrink text size globally
2019-09-14 all DDR data signals routed, routing address
2019-09-22 DDR: data lines are set, address lines are f'd. gonna try routing from the right
2019-09-23 all ddr address lines routed ???
2019-09-24 finished DDR pinswaps, about to reposition chips closer to each other, and closer to the FPGA
2019-10-11 low 2 ddr3 bytes delay matched WRT package flight time
2019-10-12 widened serpentine routing consistant with guidelines (3x trace-to-plane) need to do data byte 2 and all address lines
2019-10-12 finished ddr length matching git add -A!
2019-10-15 about to remove ZIF screen connector in favor of UNO + RPI
2019-10-15 added arduino header, shifted components, deleted 50pin ZIF, deleted MIDI in for fear of confusion with headphone jack
2019-10-28 routed most of HDMI, I2S, and Arduino-type interfaces
2019-11-06 routed a few things, about to remove power jack and 5V regulator
2019-11-09 downto 70 unrouted. moved SD interface back to MIO
2019-11-13 DRC passes with only GNDTIE errors. no unconnected. power plane quality unknown
2019-11-16 moved power to proper buried layers, about to swap layers to match 08J
2019-11-17 about to finish BOM
2019-11-29 length matched important interfaces, added current sense resistors to regulators, about to shrink silkscreen designators
2019-12-04 finished review with gerber output. still need to relocate rangefinders / LEDs
2019-12-14 some part changes for BOM clarification
2019-12-24 replaced mems mic and changed pour clearance to 5mil. caused many disconnects
2020-04-17 renamed audio signals
2020-04-17 hmmm
2020-04-17 Update withTranslate.gvp???
2020-09-24 pdating for transfer
2021-02-21 includes images
2021-02-21 removed backup files
2021-02-21 somehow the zones got messed up. fixing them
2021-03-03 updated gerbers and included schematic.pdf
2021-03-03 added block diagram and kicad logo
2021-11-06 Create LICENSE

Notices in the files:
parts and their libraries:
Copyright 2016 Accelerated Designs. All rights reserved.
